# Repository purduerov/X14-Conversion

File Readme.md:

# Readme for X14-Conversion

Whenever you make a new part, download the datasheet and save it here _**and**_ with the part in the parts library

Always pull other people's changes before beginning to work
`git pull`

Be sure to push your changes after  working on them. Run:
1. `git add .` to add any files in this directory or a subdirectory
or `git add -u` to add any modified files
2. (Optional) `git clean -nX` to see what ignored files can be removed
	`git clean -fX` removes ignored files (Eagle backups)
3. `git commit -m "helpful commit message"` with a description of the work that you did
4. `git push` to push your work to github

Other helpful commands
* `git status` says information about modified and staged files
* `git log` shows the recent commits of the repository
* `git log filename.extension` show the recent commits for just that file
* `git checkout first-couple-letter-of-commit-id` lets you go back to a previous version
* `git checkout master` brings you back to the latest commit
* `git tag` lists the tags
* `git tag -a orderX -m "the version of the board placed for the X'th order"` tag a specific commit
* `git push --tags` needed to push tags to remote
* `git show orderX` show the commit log for the given tag
* `git checkout orderX` go back and interact with the files at the tagged commit

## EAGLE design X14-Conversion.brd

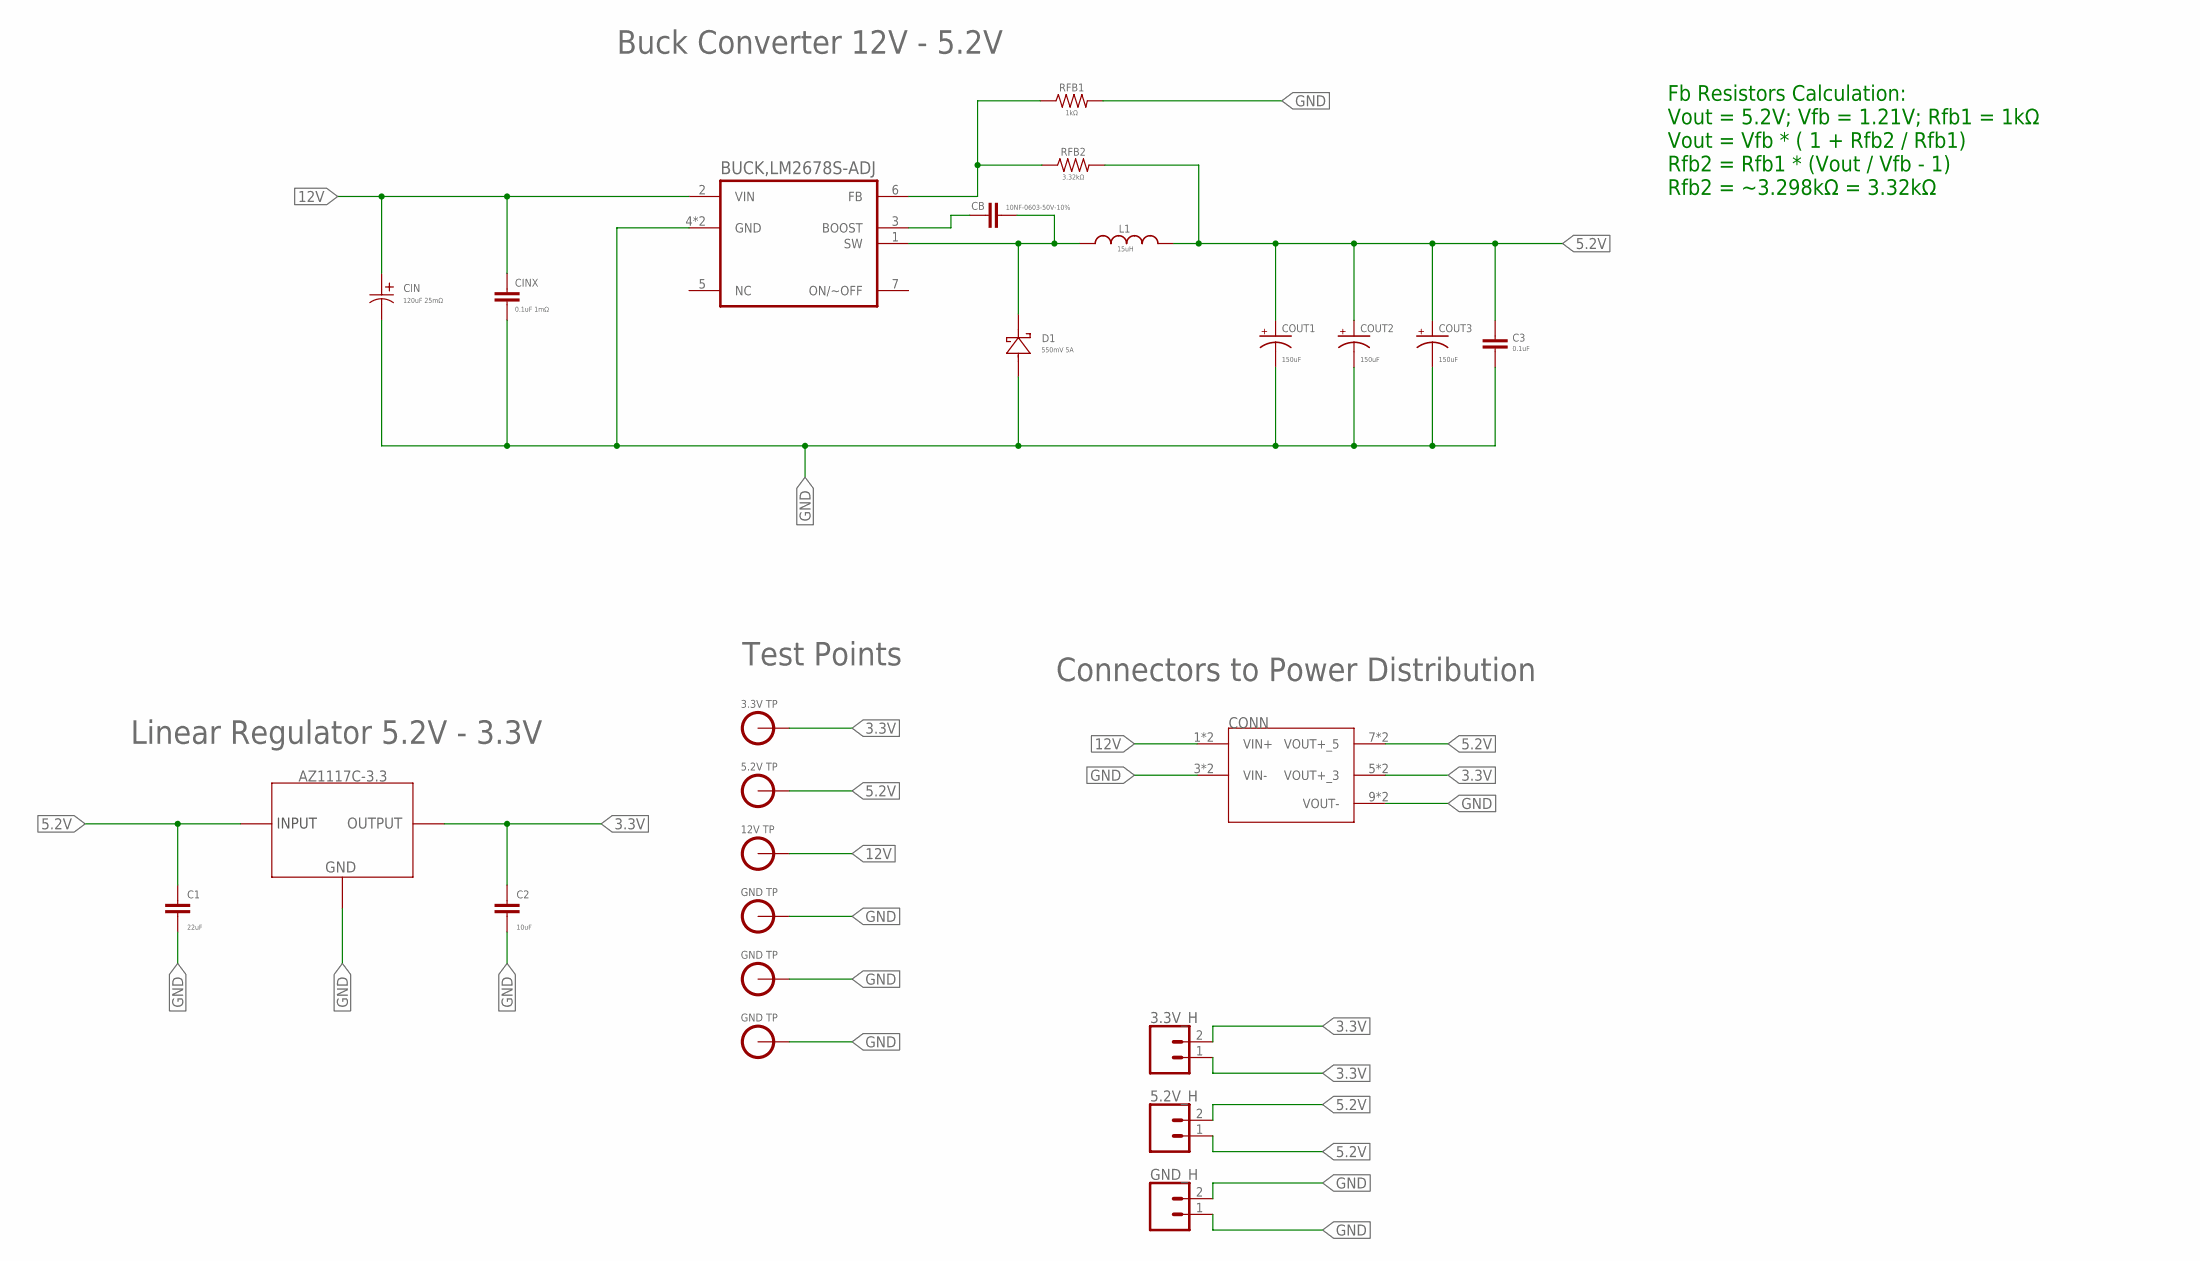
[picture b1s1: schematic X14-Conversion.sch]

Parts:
3.3V_H, 5.2V_H: CONN_02; 1X02
AZ1117C: AZ1117C-3.3; SOT150P410X160-3N
C1: 22uF; 0805
C2: 10uF; 0603
C3: 0.1uF; 0603
CB: 10NF-0603-50V-10%; 0603
CIN: 120uF 25mΩ; PCAP_SVP_C6_PAN
CINX: 0.1uF 1mΩ; 0603
CONN: CONVERSION-DISTRIBUTION; TSW-105-05-G-S(C-D)
COUT1, COUT2, COUT3: 150uF; 2917(7343-31-METRIC)
D1: 550mV 5A; CDBG520-G
GND_H: CONN_02; 1X02
L1: 15uH; HCMA1305
RFB1: 1kΩ; 0603
RFB2: 3.32kΩ; 0603
U1: BUCK,LM2678S-ADJ; TO127P1435X464-8N
U$2: 3.3V_TESTPOINT
U$3: 5.2V_TESTPOINT
U$4: 12V_TESTPOINT
U$5, U$6, U$7: GND_TESTPOINT

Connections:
3.3V: 3.3V_H.1, 3.3V_H.2, AZ1117C.2 (OUTPUT), AZ1117C.4 (OUTPUT), C2.1, CONN.5 (VOUT+_3), CONN.6 (VOUT+_3), U$2.3.3V
5.2V: 5.2V_H.1, 5.2V_H.2, AZ1117C.3 (INPUT), C1.1, C3.1, CONN.7 (VOUT+_5), CONN.8 (VOUT+_5), COUT1.+, COUT2.+, COUT3.+, L1.2, RFB2.2, U$3.5.2V
12V: CIN.1, CINX.1, CONN.1 (VIN+), CONN.2 (VIN+), U1.2 (VIN), U$4.12V
CB: CB.1, U1.3 (BOOST)
FB: RFB1.1, RFB2.1, U1.6 (FB)
GND: AZ1117C.1 (GND), C1.2, C2.2, C3.2, CIN.2, CINX.2, CONN.3 (VIN-), CONN.4 (VIN-), CONN.9 (VOUT-), CONN.10 (VOUT-), COUT1.-, COUT2.-, COUT3.-, D1.2, GND_H.1, GND_H.2, RFB1.2, U1.4 (GND), U1.8 (GND), U$5.GND, U$6.GND, U$7.GND
SW: CB.2, D1.1, L1.1, U1.1 (SW)

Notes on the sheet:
Buck Converter 12V - 5.2V
Connectors to Power Distribution
Linear Regulator 5.2V - 3.3V
Test Points
Fb Resistors Calculation: Vout = 5.2V; Vfb = 1.21V; Rfb1 = 1kΩ Vout = Vfb * ( 1 + Rfb2 / Rfb1) Rfb2 = Rfb1 * (Vout / Vfb - 1) Rfb2 = ~3.298kΩ = 3.32kΩ

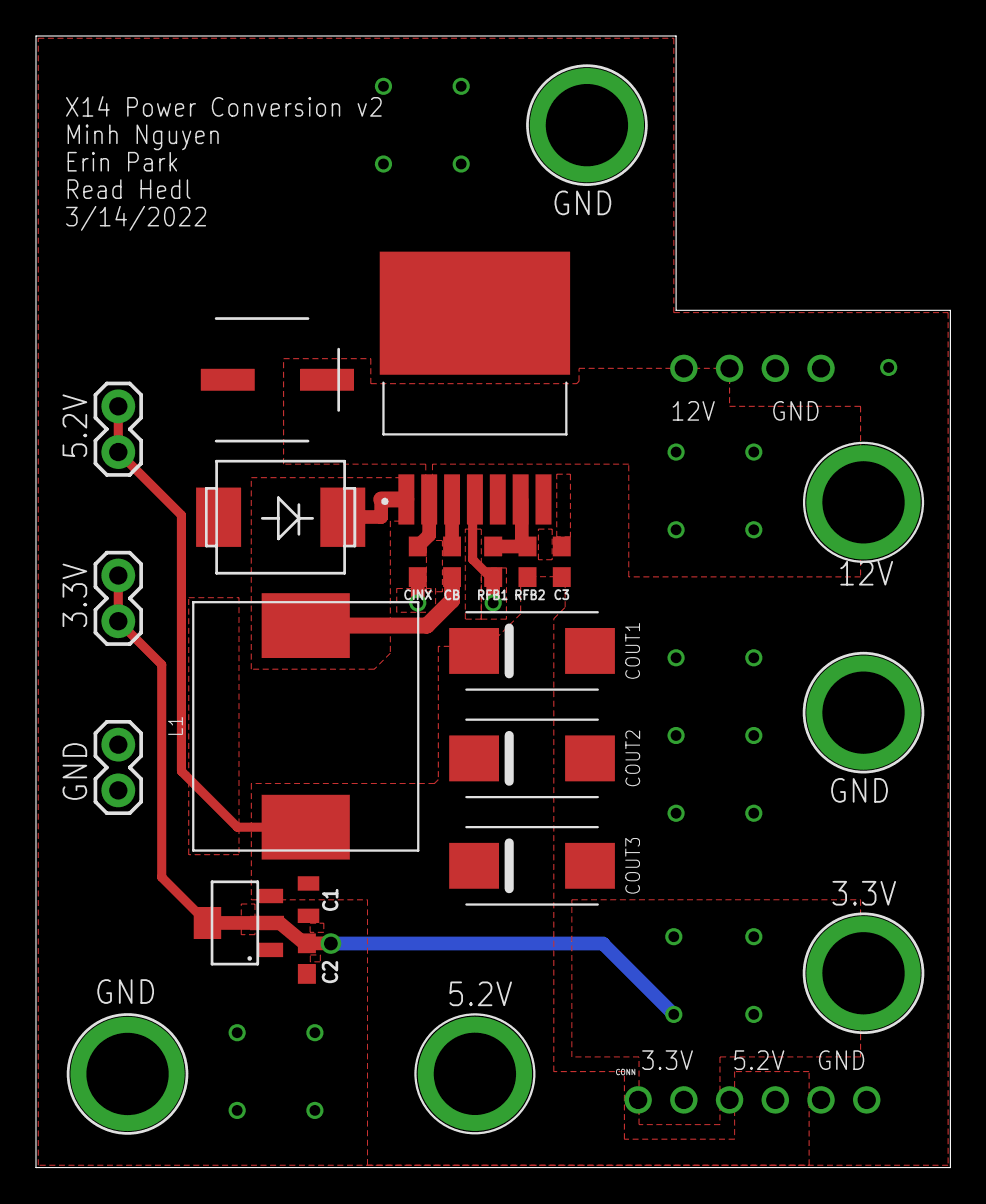
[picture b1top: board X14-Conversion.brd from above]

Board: 2 copper layers, 50.8 x 62.9 mm, 25 parts (1 on the bottom side), 7 nets.

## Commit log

2021-09-18 readme+gitignore
2021-10-02 Created files
2021-10-13 Added conversion board library
2021-10-14 Update new parts library
2021-10-14 Complete Schematic for LM2678
2021-10-20 Fix Schematic
2021-10-20 Completing Schematic
2021-10-20 Completing Schematic (1) and Upload Datasheets
2021-10-21 Update Datasheets Library and Finalize schematics
2021-10-30 Fix Schematic, add test points, screw terminals and connectors
2021-11-06 Fix capacitors and resistors to Sparkfun components
2021-11-06 Fix capacitors on Linear Regulator
2021-11-06 Fix Footprints
2021-11-11 Fix footprints and update dimension
2021-11-21 Complete Board Layout
2021-11-28 Completet Board Layout (1)
2021-11-30 Fix Board Layout
2021-12-01 isolate updated
2021-12-04 Fix Board
2021-12-04 Fix 45 Degree and minor details
2021-12-04 Finalizing board for Alumni Design Review
2021-12-04 Fix Testpoints
2021-12-04 Fix board with new DRC
2021-12-17 Change Output Capacitors
2021-12-18 Fix & complete board
2021-12-20 Complete Board
2021-12-24 final
2022-01-02 Fix board layout based on Grant's comments
2022-01-04 small adjustments
2022-01-07 added silkscreen
2022-01-26 STEPS!
2022-03-10 Reduce board size
2022-03-14 add 1x2 headers to board
2022-03-14 Adjusted Label, Exported STEP
2022-03-14 fixed STP file
2022-04-14 Update label position

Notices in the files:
parts and their libraries:
SparkFun-Capacitors: Licensing: Creative Commons ShareAlike 4.0 International - https://creativecommons.org/licenses/by-sa/4.0
